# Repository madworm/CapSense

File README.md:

CapSense
========

LAYOUT FILES: Capacitive sensing experiments.

---

Before having PC-boards made, please make sure you know about your manufacturer's peculiarities!
Especially drill-sizes and their tolerances may vary too much and give you trouble.

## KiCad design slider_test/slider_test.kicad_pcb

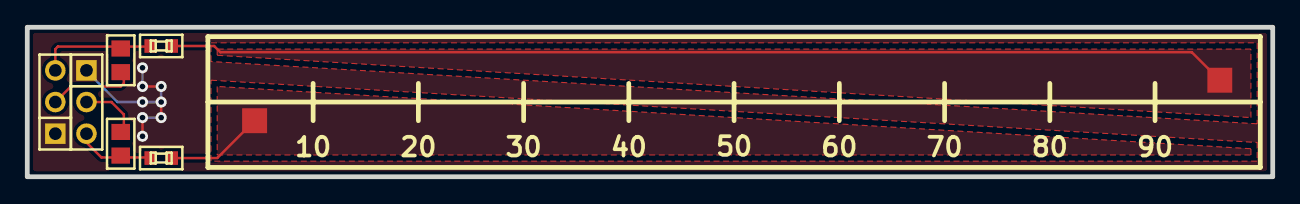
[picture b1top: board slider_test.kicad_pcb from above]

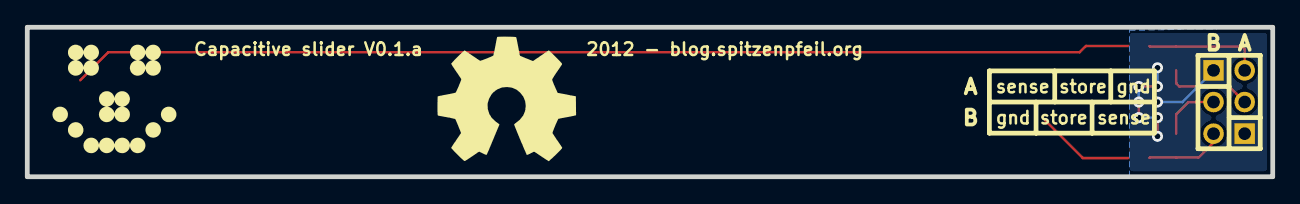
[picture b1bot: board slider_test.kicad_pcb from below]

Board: 2 copper layers, 100.0 x 12.0 mm, 10 parts (2 on the bottom side), 7 nets.

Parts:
C1, C2: 20nF; MADW__C0805
CS1, CS2: slider; MADW__SIL-3
G1: LOGO
G2: LOGO
R1, R2: 1k; MADW__R0603_2
TP1, TP2: TST; MADW__SIL-1

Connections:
/pad_a: R1.2, TP1.1
/pad_a_sense: C1.2, CS1.3, R1.1
/pad_a_store: C1.1, CS1.2
/pad_b: R2.2, TP2.1
/pad_b_sense: C2.2, CS2.3, R2.1
/pad_b_store: C2.1, CS2.2
GND: CS1.1, CS2.1

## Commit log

2012-07-17 Stuff
2012-07-17 First doodles.
2012-07-18 More doodles.
2012-07-18 Getting there...
2012-07-18 Added a bit of purpleness.
2012-07-18 Removed the GND pour underneath (backside) of the sensor pads.
2012-09-03 Updated .gitignore
2013-01-17 Added README.md
2013-01-23 Increased drill size for pin-headers to 40mil.
    Did NOT recreate gerber files!
2013-01-23 Changed library path, so it doesn't use a symlink anymore.
2013-01-24 Recreated the gerber files (40mil drill size issue).
2014-06-02 Added sample code for the slider.
2014-06-02 ./slider_test: converted to new board format + little tweaks.
